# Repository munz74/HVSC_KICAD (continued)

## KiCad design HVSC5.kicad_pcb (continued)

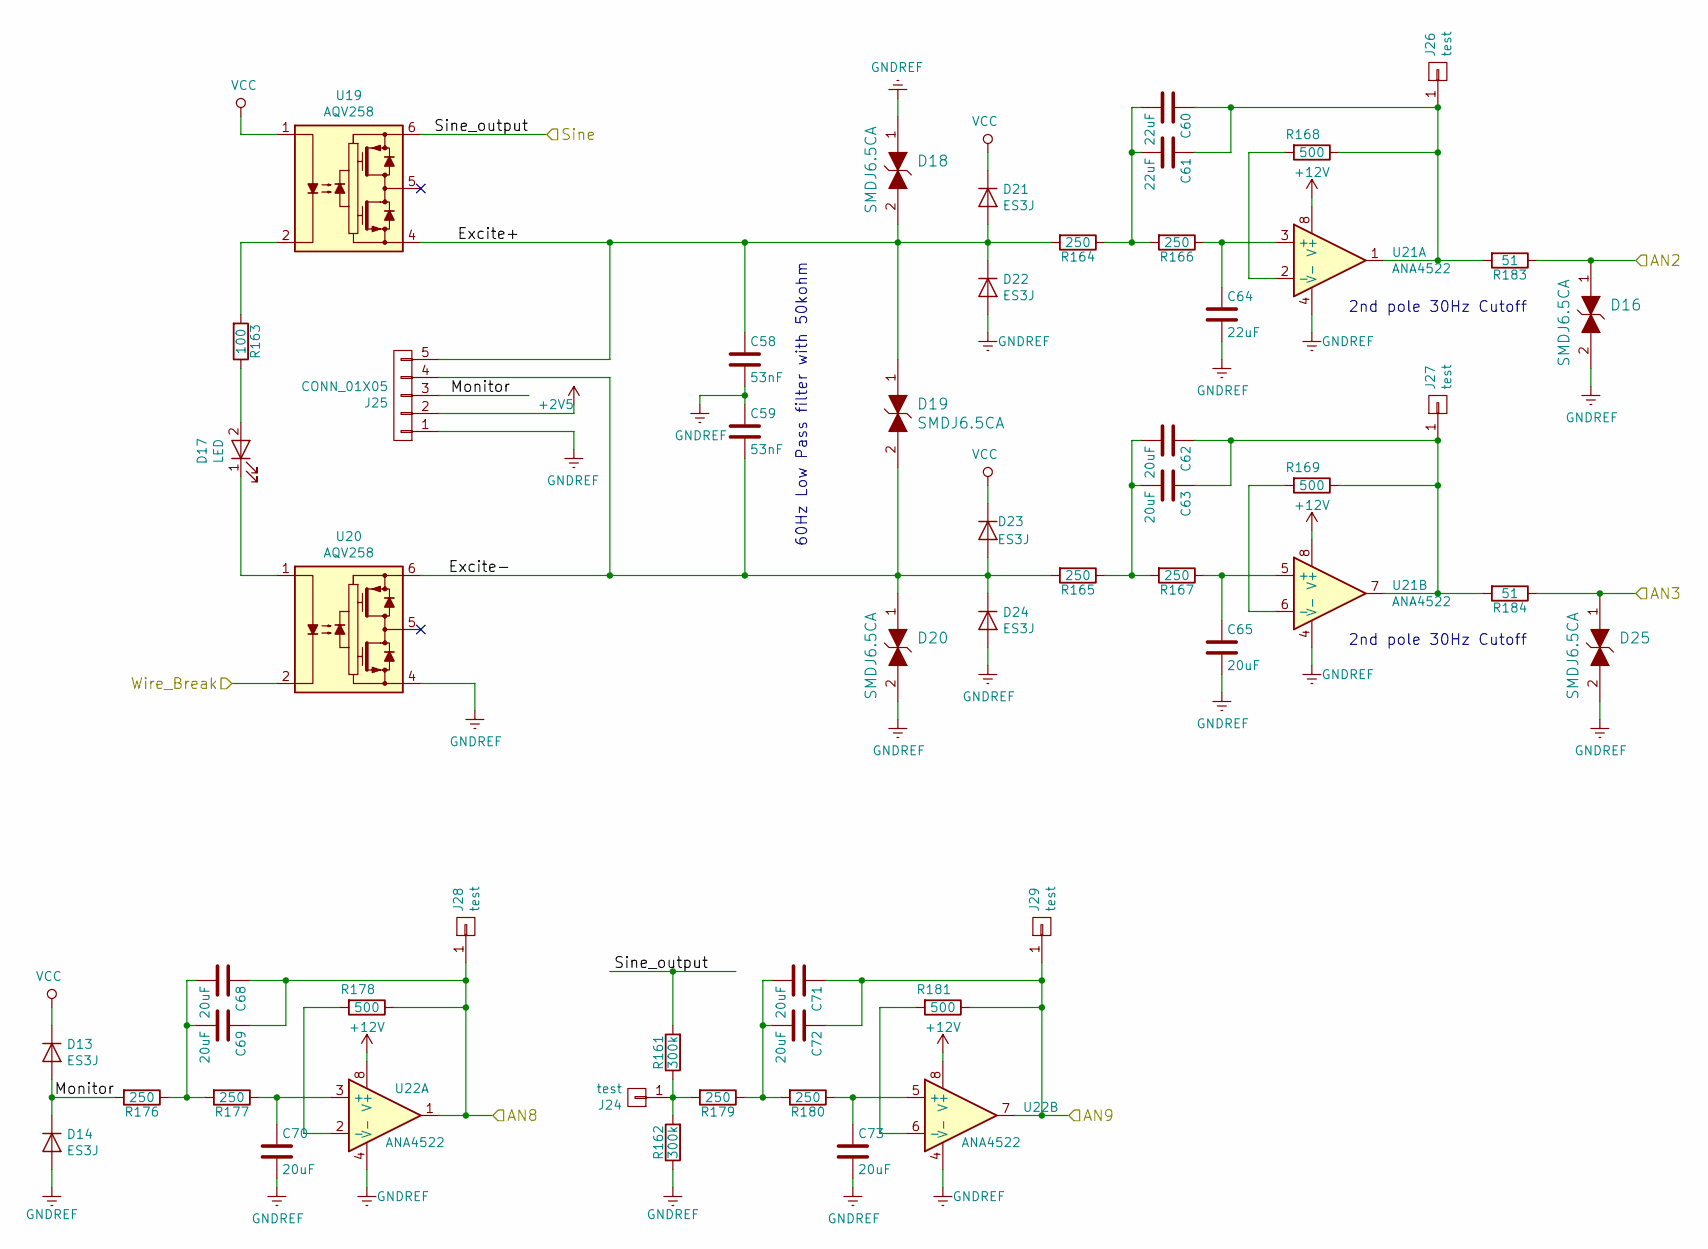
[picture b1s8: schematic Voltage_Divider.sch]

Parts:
C58, C59: 53nF; C_1210_HandSoldering
C60, C61, C64: 22uF; C_1210_HandSoldering
C62, C63, C65, C68, C69, C70, C71, C72, C73: 20uF; C_1210_HandSoldering
D13, D14, D21, D22, D23, D24: ES3J; D_SMC_Handsoldering
D16, D18, D19, D20, D25: SMDJ6.5CA; D_SMC_Handsoldering; MPN PGB1010603MR; Digi-Key_PN F2594CT-ND
D17: LED; LED_D5.0mm
J24, J26, J27, J28, J29: test; Pin_Header_Straight_1x01_Pitch2.00mm
J25: CONN_01X05; M53259-5
R161, R162: 300k; R_Axial_DIN0207_L6.3mm_D2.5mm_P10.16mm_Horizontal
R163: 100; R_0805_HandSoldering
R164, R165, R166, R167, R176, R177, R179, R180: 250; R_0805_HandSoldering
R168, R169, R178, R181: 500; R_0805_HandSoldering
R183, R184: 51; R_0805_HandSoldering
U19, U20: AQV258; DIP-6_W7.62mm_Socket
U21, U22: ANA4522; SOIC-8_3.9x4.9mm_Pitch1.27mm

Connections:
+2V5: J25.2; also elsewhere on the board
+12V: U21.8 (V+), U22.8 (V+); also elsewhere on the board
/ADC7175/AIN2: D16.1, R183.1; also elsewhere on the board
/ADC7175/AIN3: D25.1, R184.1; also elsewhere on the board
/ADC7175/AIN8: C68.1, C69.1, J28.1, R178.1, U22.1; also elsewhere on the board
/ADC7175/AIN9: C71.1, C72.1, J29.1, R181.1, U22.7; also elsewhere on the board
/Monitor/Sine: R161.2, U19.6 (VCC); also elsewhere on the board
/Voltage_Divider/Excite+: C58.1, D18.2, D19.1, D21.2 (A), D22.1 (K), J25.5, R164.2, U19.4 (VEE)
/Voltage_Divider/Excite-: C59.2, D19.2, D20.1, D23.2 (A), D24.1 (K), J25.4, R165.2, U20.6 (VCC)
/Voltage_Divider/Sine_APP: U20.2 (C); also elsewhere on the board
GNDREF: C58.2, C59.1, C64.2, C65.2, C70.2, C73.2, D14.2 (A), D16.2, D18.1, D20.2, D22.2 (A), D24.2 (A), D25.2, J25.1, R162.1, U20.4 (VEE), U21.4 (V-), U22.4 (V-); also elsewhere on the board
unnamed: C60.1, C61.1, J26.1, R168.1, R183.2, U21.1
unnamed: C60.2, C61.2, R164.1, R166.2
unnamed: C62.1, C63.1, J27.1, R169.1, R184.2, U21.7
unnamed: C62.2, C63.2, R165.1, R167.2
unnamed: C64.1, R166.1, U21.3 (+)
unnamed: C65.1, R167.1, U21.5 (+)
unnamed: C68.2, C69.2, R176.1, R177.2
unnamed: C70.1, R177.1, U22.3 (+)
unnamed: C71.2, C72.2, R179.1, R180.2
unnamed: C73.1, R180.1, U22.5 (+)
unnamed: D17.1 (K), U20.1 (A)
unnamed: D17.2 (A), R163.1
unnamed: J24.1, R161.1, R162.2, R179.2
unnamed: R163.2, U19.2 (C)
unnamed: R168.2, U21.2 (-)
unnamed: R169.2, U21.6 (-)
unnamed: R178.2, U22.2 (-)
unnamed: R181.2, U22.6 (-)
VCC: D13.1 (K), D21.1 (K), D23.1 (K), U19.1 (A); also elsewhere on the board

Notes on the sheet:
2nd pole 30Hz Cutoff
60Hz Low Pass filter with 50kohm

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
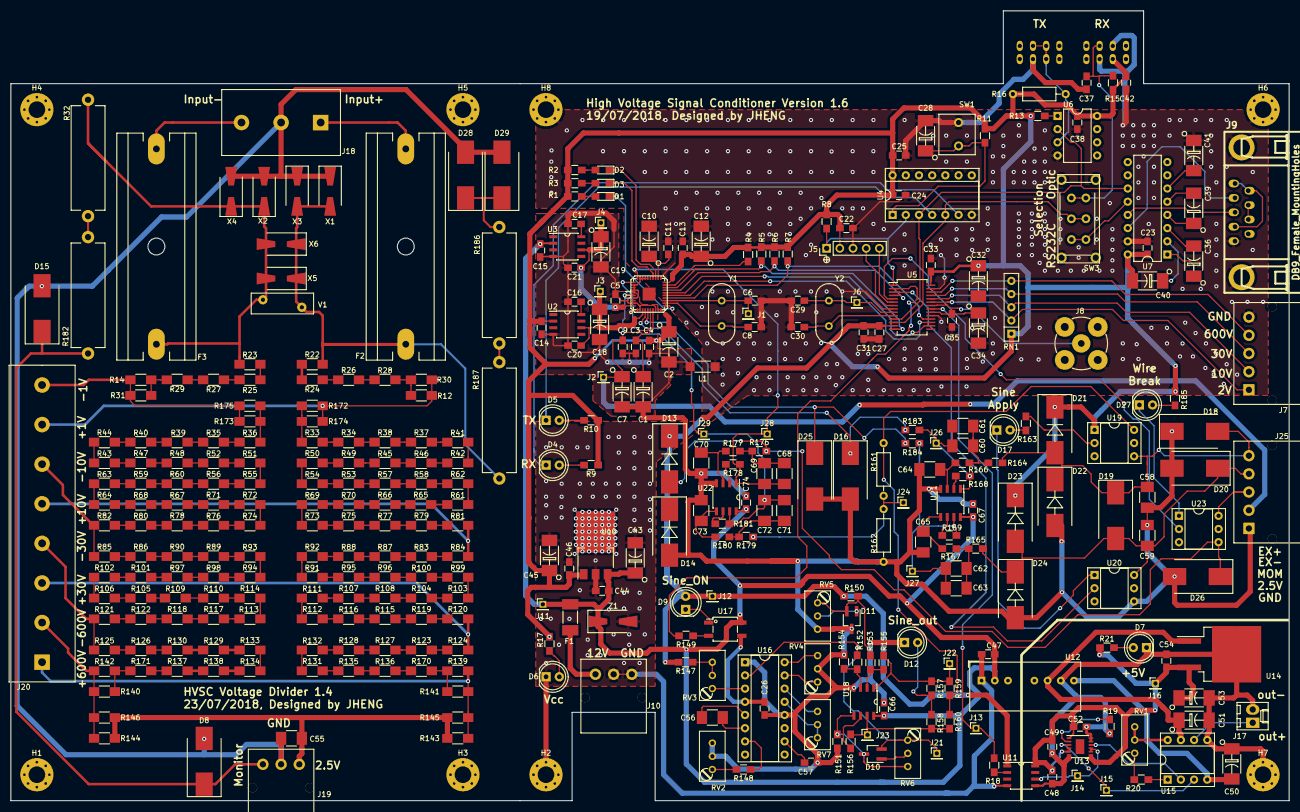
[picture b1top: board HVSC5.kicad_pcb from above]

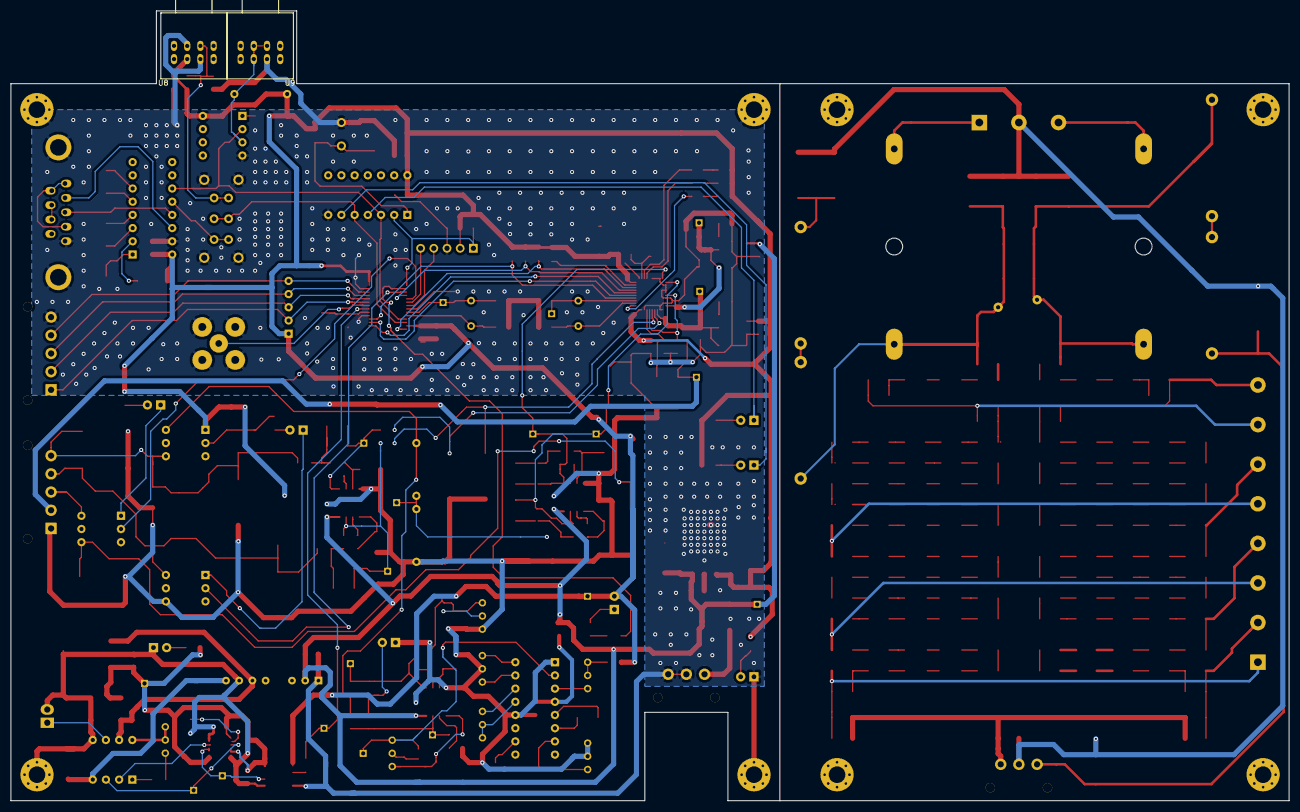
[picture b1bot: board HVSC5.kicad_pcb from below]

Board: 2 copper layers, 246.0 x 152.0 mm, 374 parts (2 on the bottom side), 261 nets.

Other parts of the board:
D26: SMDJ6.5CA; D_SMC_Handsoldering
D27: LED; LED_D5.0mm
D28, D29: SMDJ11CA; D_SMC_Handsoldering
R185: 100; R_0805_HandSoldering
R186, R187: 150k; R_Axial_Power_L20.0mm_W6.4mm_P22.40mm
U23: AQV258; DIP-6_W7.62mm_Socket

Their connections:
/Voltage_Divider/Wire_Break: U23.2; also elsewhere on the board
GNDREF: D26.2, D28.2, D29.2; also elsewhere on the board
unnamed: D27.1, U23.1
unnamed: D27.2, R185.1
unnamed: D28.1, D29.1, R186.2
unnamed 94: R187.1; also elsewhere on the board
unnamed: R186.1, R187.2
VCC: R185.2; also elsewhere on the board

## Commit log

2018-06-06 2차 PCB
    2차 PCB 발주 버전 에서 아주 조금 수정한것
2018-06-06 Small_Change
    시험삼아서 수정하였음
2018-06-06 저항값설정
    저항값 1차 설정
2018-06-07 Soldering sequence
    솔더링 순서
    1st CPU PW ADC
    2nd Filter
    3rd DAC out
    4th Sine generator
    5th Voltage divider & protection
2018-06-08 전해콘덴서 foot print 변경
    전해 콘덴서 변경
    Bypass 콘데서 OPAMP에 추가 하여야 함
2018-06-11 2차 PCB 1차 수정
    1. ADR455 Vcc V12 수정
    2. DCDC 입력전압 변경
    3. Bypass 콘덴서 C66, C67 추가
    4. SOIC 방향 표시
    5. TLV431 PADS 변경
    6. AQV258 Pin3 --> Pin2
2018-06-12 switch 수정
2018-06-12 Selector 표시
2018-06-14 Selector Numbering
    Selector numbering
2018-06-18 0805_넓히기
    기타 수정
2018-06-18 1206 update
    다시 보세요.
2018-06-22 2차PCB
    U22 포함
2018-07-04 High Voltage reinforce
    고전압 부분 보강
    AN2, AN3 두 부분 6.5V limit
2018-07-13 3차 PCB
    1. 모니터 고압부 150k옴 2갤로 수정
    2. 6.5V Zener 추가
2018-07-16 PCB Part name
    PCB Part name 수정
2018-07-19 4차 PCB
    U23 Wire Breakage Relay 추가
2018-07-23 Balanced Resistor 추가
    D28 D29, R186, R187 추가
